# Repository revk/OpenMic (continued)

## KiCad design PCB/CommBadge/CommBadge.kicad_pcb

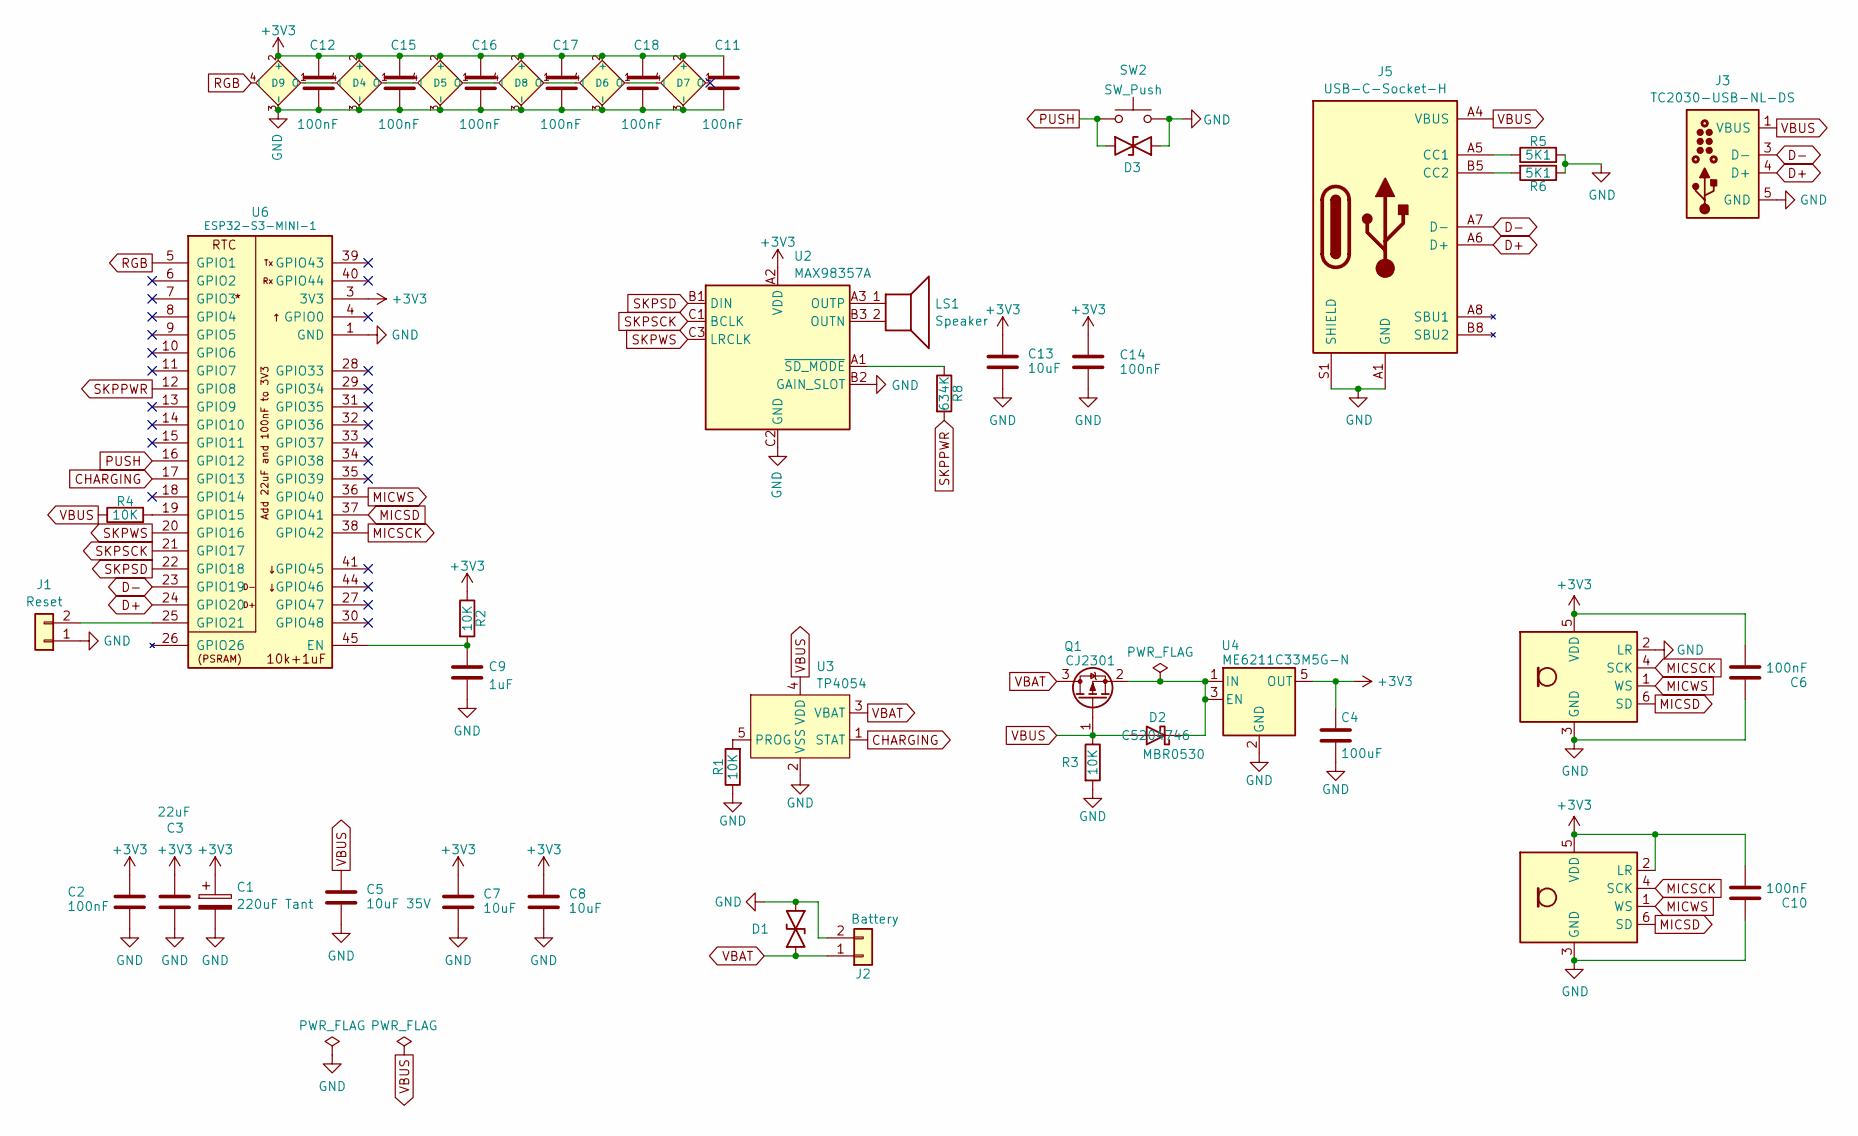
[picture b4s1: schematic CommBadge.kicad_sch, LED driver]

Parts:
C1: 220uF Tant
C2, C6, C10, C11, C12, C14, C15, C16, C17, C18: 100nF
C3: 22uF
C4: 100uF
C5: 10uF 35V
C7, C8, C13: 10uF
C9: 1uF
D1, D3: DFN1006-2L; MPN C5137770
D2: MBR0530; MPN C5204746
D4, D5, D6, D7, D8, D9: XL-1010RGBC-WS2812B; MPN C5349953
J1: Reset
J2: Battery
J3: TC2030-USB-NL-DS; Tag-Connect_TC2030-IDC-NL_2x03_P1.27mm_Vertical
J5: USB-C-Socket-H; MPN C709357
LS1: Speaker
Q1: CJ2301; SOT-23
R1, R2, R3, R4: 10K
R5, R6: 5K1
R8: 634K
SW2: SW_Push
U2: MAX98357A; WLP-1.437mmx1.347mm-0.21mm-ball; MPN C2682619
U3: TP4054; SOT-23-5; MPN C668215
U4: ME6211C33M5G-N; SOT-23-5
U5: L; ICS43434_MEMS_Mic_Open; MPN C5656610
U6: ESP32-S3-MINI-1; MPN C3013941
U7: R; ICS43434_MEMS_Mic_Open; MPN C5656610

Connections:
+3V3: C1.1, C2.1, C3.1, C4.1, C6.2, C7.1, C8.1, C10.2, C11.1, C12.1, C13.1, C14.1, C15.1, C16.1, C17.1, C18.1, D4.2 (+), D5.2 (+), D6.2 (+), D7.2 (+), D8.2 (+), D9.2 (+), R2.1, U2.A2 (VDD), U4.5 (OUT), U5.5 (VDD), U6.3 (3V3), U7.2 (LR), U7.5 (VDD)
CHARGING: U3.1 (STAT), U6.17 (GPIO13)
D+: J3.4 (D+), J5.A6 (D+), J5.B6 (D+), U6.24 (GPIO20)
D-: J3.3 (D-), J5.A7 (D-), J5.B7 (D-), U6.23 (GPIO19)
GND: C1.2, C2.2, C3.2, C4.2, C5.2, C6.1, C7.2, C8.2, C9.2, C10.1, C11.2, C12.2, C13.2, C14.2, C15.2, C16.2, C17.2, C18.2, D1.1, D3.1, D4.3 (-), D5.3 (-), D6.3 (-), D7.3 (-), D8.3 (-), D9.3 (-), J1.1, J2.2, J3.5 (GND), J3.6 (GND), J5.A1 (GND), J5.A12 (GND), J5.B1 (GND), J5.B12 (GND), J5.S1 (SHIELD), R1.1, R3.2, R5.2, R6.1, SW2.1, U2.B2 (GAIN_SLOT), U2.C2 (GND), U3.2 (VSS), U4.2 (GND), U5.2 (LR), U5.3 (GND), U6.1 (GND), U6.2 (GND), U6.42 (GND), U6.43 (GND), U6.46 (GND), U6.47 (GND), U6.48 (GND), U6.49 (GND), U6.50 (GND), U6.51 (GND), U6.52 (GND), U6.53 (GND), U6.54 (GND), U6.55 (GND), U6.56 (GND), U6.57 (GND), U6.58 (GND), U6.59 (GND), U6.60 (GND), U6.61 (GND), U6.62 (GND), U6.63 (GND), U6.64 (GND), U6.65 (GND), U7.3 (GND)
MICSCK: U5.4 (SCK), U6.38 (GPIO42), U7.4 (SCK)
MICSD: U5.6 (SD), U6.37 (GPIO41), U7.6 (SD)
MICWS: U5.1 (WS), U6.36 (GPIO40), U7.1 (WS)
unnamed: D2.1 (K), Q1.2 (S), U4.1 (IN), U4.3 (EN)
unnamed: D4.4 (I), D9.1 (O)
unnamed: D4.1 (O), D5.4 (I)
unnamed: D5.1 (O), D8.4 (I)
unnamed: D6.4 (I), D8.1 (O)
unnamed: D6.1 (O), D7.4 (I)
unnamed: J1.2, U6.25 (GPIO21)
unnamed: J5.A5 (CC1), R5.1
unnamed: J5.B5 (CC2), R6.2
unnamed: LS1.2, U2.B3 (OUTN)
unnamed: LS1.1, U2.A3 (OUTP)
unnamed: R8.1, U2.A1 (~SD_MODE)
unnamed: R1.2, U3.5 (PROG)
unnamed: C9.1, R2.2, U6.45 (EN)
unnamed: R4.2, U6.19 (GPIO15)
PUSH: D3.2, SW2.2, U6.16 (GPIO12)
RGB: D9.4 (I), U6.5 (GPIO1)
SKPPWR: R8.2, U6.12 (GPIO8)
SKPSCK: U2.C1 (BCLK), U6.21 (GPIO17)
SKPSD: U2.B1 (DIN), U6.22 (GPIO18)
SKPWS: U2.C3 (LRCLK), U6.20 (GPIO16)
VBAT: D1.2, J2.1, Q1.3 (D), U3.3 (VBAT)
VBUS: C5.1, D2.2 (A), J3.1 (VBUS), J3.2 (VBUS), J5.A4 (VBUS), J5.A9 (VBUS), J5.B4 (VBUS), J5.B9 (VBUS), Q1.1 (G), R3.1, R4.1, U3.4 (VDD)

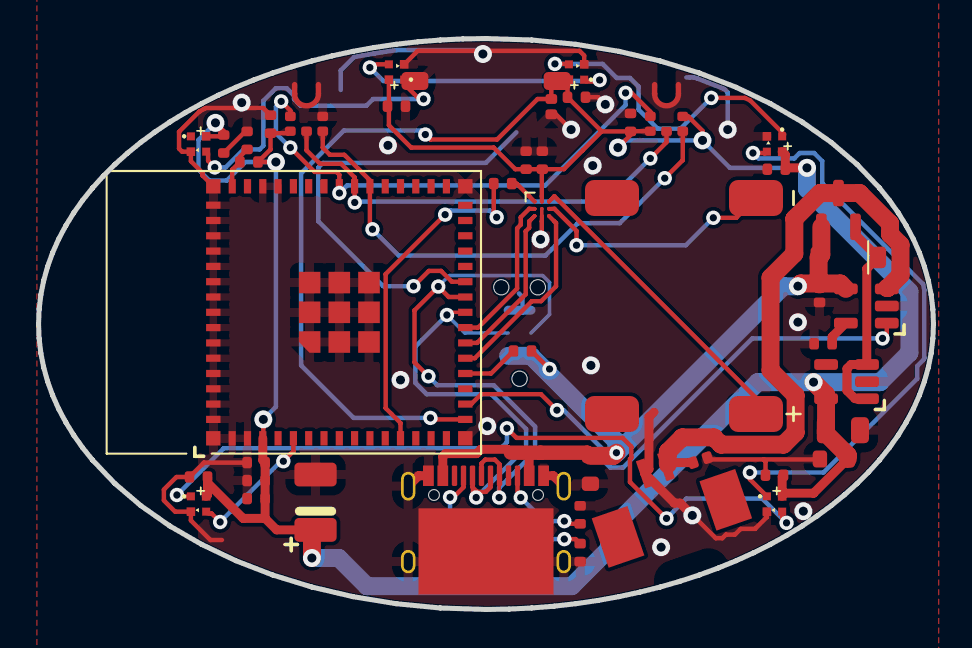
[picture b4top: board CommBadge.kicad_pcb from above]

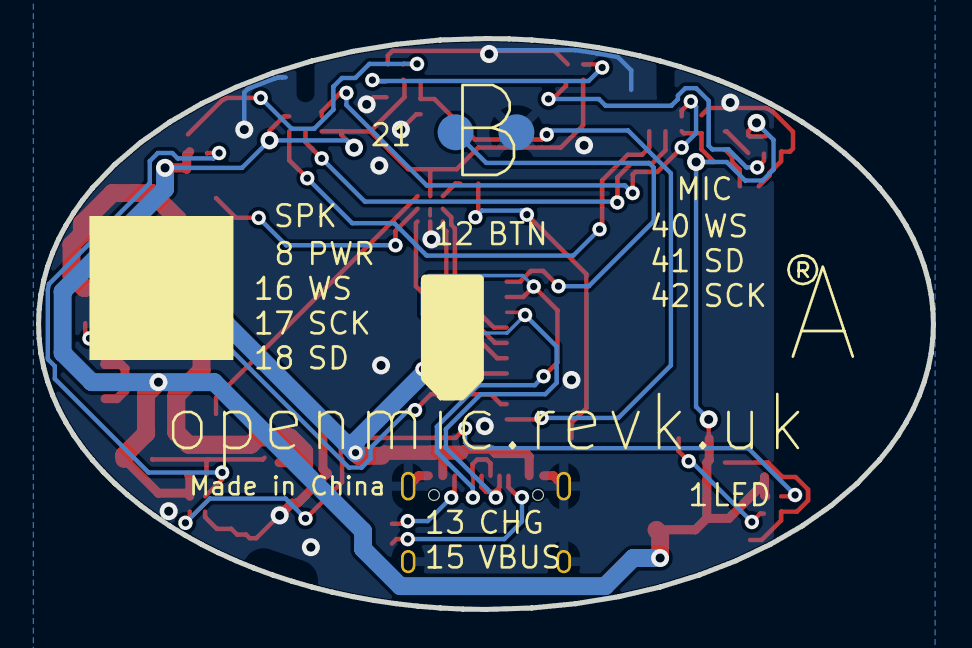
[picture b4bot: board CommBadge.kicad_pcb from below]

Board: 2 copper layers, 49.7 x 31.7 mm, 47 parts (2 on the bottom side), 31 nets.

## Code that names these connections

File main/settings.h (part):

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 uint8_t meshroot:1;	// This is preferred mesh root
#endif
};
extern revk_gpio_t spkpwr;	// Speaker power on
extern revk_gpio_t spklrc;	// Speaker LR clock
extern revk_gpio_t spkbclk;	// Speaker Bit clock
extern revk_gpio_t spkdata;	// Speaker Data
extern revk_gpio_t micdata;	// Microphone Data / SD
extern revk_gpio_t micclock;	// Microphone Clock / SCK
extern revk_gpio_t micws;	// Microphone WS (not set for PDM)
extern uint32_t micrate;	// Microphone Input rate (when not SIP)
extern uint8_t micgain;	// Microphone Multiply input (set 0 for 24 bit raw)
#define	micstereo	revk_settings_bits.micstereo
#define	micright	revk_settings_bits.micright
#define	micbeep	revk_settings_bits.micbeep
extern revk_gpio_t sddat2;	// MicroSD DAT2
extern revk_gpio_t sddat3;	// MicroSD DAT3
extern revk_gpio_t sdcmd;	// MicroSD CMD
extern revk_gpio_t sdclk;	// MicroSD CLK
extern revk_gpio_t sddat0;	// MicroSD DAT0
extern revk_gpio_t sddat1;	// MicroSD DAT1
extern revk_gpio_t sdcd;	// MicroSD CD
extern uint32_t sdrectime;	// Max record time per whole file
extern uint32_t sdsynctime;	// Max record time per file sync
extern char* sdupload;	// Where to post, then delete, files on power off
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extern uint32_t autooff;	// Auto power off if idle
#define	autousb	revk_settings_bits.autousb
extern revk_gpio_t button;	// Button
extern revk_gpio_t charging;	// Charging status
extern revk_gpio_t vbus;	// USB power status
extern revk_gpio_t irgpio;	// IR receiver
extern revk_gpio_t rgbstatus;	// Status LED
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#define	prefixhost	revk_settings_bits.prefixhost
#ifdef	CONFIG_REVK_BLINK_DEF
#ifdef	CONFIG_REVK_BLINK_WS2812_DEF
extern revk_gpio_t blink;	// WS2812 LED
#else
extern revk_gpio_t blink[3];	// R, G, B LED array (set all the same for WS2812 LED)
#endif
#endif
#ifdef  CONFIG_REVK_APMODE
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
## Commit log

2024-12-22 Library update
2024-12-22 betarelease
2024-12-22 Code size
2024-12-22 Image
2024-12-22 Simpler
2024-12-22 LED better
2024-12-22 LEDs
2024-12-22 Tidy
2024-12-22 button
2024-12-22 No sleep if no button
2024-12-25 Try that
2024-12-25 Deregister
2024-12-27 Logging
2024-12-27 Debug
2024-12-27 Remove debug
2024-12-27 Tidy LED
2024-12-28 Dark mode should be dark when recording!
2025-01-01 HA on keeps wifi on
2025-01-04 Started on STL (needs more work)
2025-01-04 Working on STL
2025-01-04 Submodule
2025-01-04 Cleaner STL
2025-01-04 Cleaner
2025-01-04 Not sure it is right yet
2025-01-08 Icon
2025-01-09 light
2025-01-09 Testing
2025-01-09 Nice HA button and status report
2025-01-12 Images
2025-01-13 Re render
2025-01-13 New settings/release
2025-01-14 Re-order
2025-01-21 No point
2025-01-21 Release
2025-01-21 Width
2025-01-21 Re-render
2025-01-21 Colour
2025-01-22 Tweak SS
2025-01-22 Cleaner readme
2025-01-22 Tidy readme
2025-01-22 Cleanup for latest kicad
2025-01-22 Fucking KiCAD changes
2025-01-23 PCB Update
2025-01-26 Mic check and blue for idle
2025-01-26 Mic check
2025-01-26 Beta
2025-02-07 Recorder GPIO and new PCBs
2025-02-13 Started new Intercom
2025-02-14 New PCB
2025-02-14 Render
2025-02-15 Tidy, new kicad
2025-02-15 Tinkering
2025-02-15 Logo
2025-02-26 Larger text
2025-02-27 Silk
2025-03-26 Power control for LEDs
2025-03-26 Clean up
2025-04-02 Edge
2025-04-02 LED power
2025-04-02 LED power, and update
2025-05-17 Tidy care render
2025-05-17 Blink when charging
2025-05-24 New battery case
2025-05-28 micgain=0 fix maybe
2025-05-28 Colour maybe
2025-05-30 IR handler, not really used yet
2025-05-30 TV remote
2025-07-08 New layout
2025-07-09 Tracked for order
2025-07-26 Layout tweaks
2025-07-26 Re-renber
2025-07-27 Moved GPIOs around a bit
2025-07-28 Recorder boards
2025-07-28 Defaults
2025-07-28 Started on new recorder logic
2025-07-29 Battery level
2025-07-29 Download LEDs
2025-07-29 Twqeak
2025-07-29 Not handling no bat well
2025-07-29 LEDs show beep status, and upgrade and upload
2025-07-29 Tidy non beep sync LEDs
2025-07-29 Tidy shutdown
2025-07-30 LED clean shutdown
2025-07-30 Reverse upload status
2025-07-30 Fix button
2025-08-01 Sync beep
2025-08-02 beep bug
2025-08-04 Tweak
2025-08-10 Added USB MSC option for WAV file transfer
2025-08-10 USB mode testing
2025-08-10 Cleaner USB, not 100% sure...
2025-08-10 VBUS power to USB
2025-08-10 New renders
2025-08-11 Finally USB MSC logic
2025-08-11 Re make
2025-08-11 Latest tweaks
2025-08-13 v-cut
2025-08-13 N8 pre USB
2025-08-31 Case
2025-08-31 Case fix
2025-08-31 Render as order
2025-09-01 Case render fix
2025-09-01 More cases
2025-09-01 Shallower
2025-09-02 Revised for order
2025-09-08 new GPIO
2025-09-08 USB start only if SD present
2025-09-08 USB safer
2025-09-08 needs work on case
2025-09-08 notes
2025-09-16 Clean up cases
2025-09-16 Improved mic backing
2025-09-16 Closer
2025-09-16 More tidy
2025-09-16 More tries
2025-09-16 Small holes
2025-09-17 Thicker base
2025-09-17 USB plug tidy, ish
2025-09-20 Better LED for hold to off, and better on/off logic
2025-09-30 Audio
2025-10-01 Loop
2025-10-10 New LEDs
2025-10-12 New `dim` setting instead of using `dark`
2025-10-12 Thicker light pipes
2025-10-12 ReRender
2025-10-16 Manifest
2025-10-17 serial settings
2025-10-25 micbeep causes cleaner red LED one second light
2025-10-25 Starting LED for beep cleaner
